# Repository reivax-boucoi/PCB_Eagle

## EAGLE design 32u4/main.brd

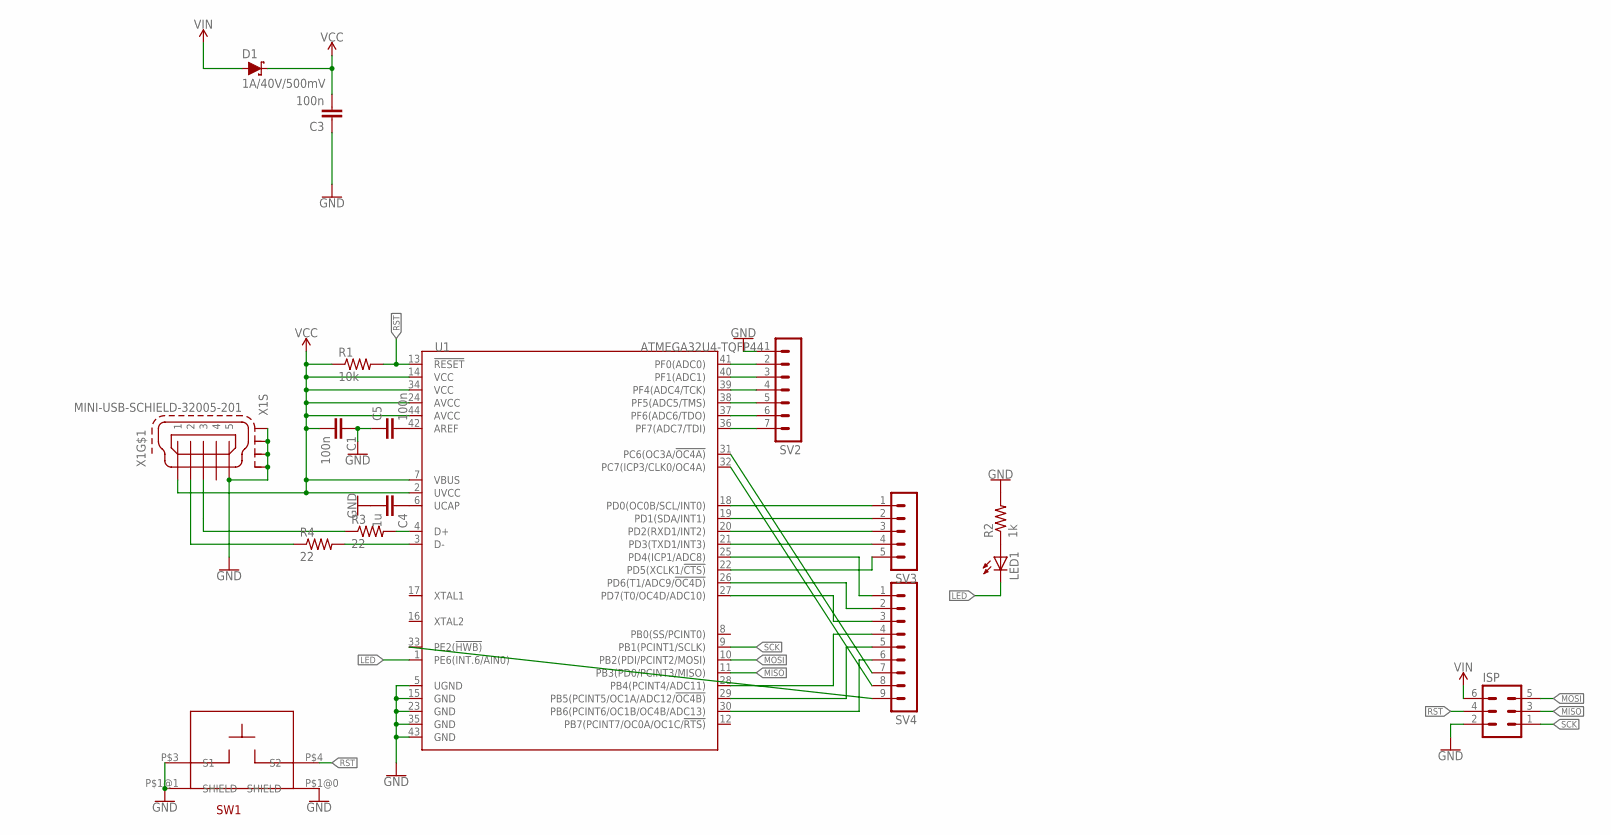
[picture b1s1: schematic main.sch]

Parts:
C1: 100n; C0402
C3, C5: 100n; C0603
C4: 1u; C0603
D1: 1A/40V/500mV; SMA-DIODE
ISP: MA03-2
LED1: LEDCHIP-LED0603; CHIP-LED0603
R1: 10k; R0603
R2: 1k; R0603
R3, R4: 22; R0603
SV2: MA07-1
SV3: MA05-1
SV4: MA09-1
SW1: TL3330
U1: ATMEGA32U4-TQFP44; TQFP44-0.8-9.6X9.6MM
X1: MINI-USB-SCHIELD-32005-201; 32005-201

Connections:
GND: C1.1, C3.1, C4.2, C5.1, ISP.2, R2.2, SV2.1, SW1.P$1@0 (SHIELD), SW1.P$1@1 (SHIELD), SW1.P$3 (S1), U1.5 (UGND), U1.15 (GND), U1.23 (GND), U1.35 (GND), U1.43 (GND), X1.5, X1.M1 (S1), X1.M2 (S2), X1.M3 (S3), X1.M4 (S4)
LED: LED1.C, U1.1 (PE6(INT.6/AIN0))
MISO: ISP.3, U1.11 (PB3(PD0/PCINT3/MISO))
MOSI: ISP.5, U1.10 (PB2(PDI/PCINT2/MOSI))
unnamed: LED1.A, R2.1
unnamed: R4.2, U1.3 (D-)
unnamed: R3.2, U1.4 (D+)
unnamed: SV3.1, U1.18 (PD0(OC0B/SCL/INT0))
unnamed: C4.1, U1.6 (UCAP)
unnamed: C5.2, U1.42 (AREF)
unnamed: SV3.2, U1.19 (PD1(SDA/INT1))
unnamed: SV3.3, U1.20 (PD2(RXD1/INT2))
unnamed: SV3.4, U1.21 (PD3(TXD1/INT3))
unnamed: R4.1, X1.2
unnamed: R3.1, X1.3
unnamed: SV3.5, U1.22 (PD5(XCLK1/!CTS))
unnamed: SV2.2, U1.41 (PF0(ADC0))
unnamed: SV2.3, U1.40 (PF1(ADC1))
unnamed: SV2.4, U1.39 (PF4(ADC4/TCK))
unnamed: SV2.5, U1.38 (PF5(ADC5/TMS))
unnamed: SV2.6, U1.37 (PF6(ADC6/TDO))
unnamed: SV2.7, U1.36 (PF7(ADC7/TDI))
unnamed: SV4.1, U1.25 (PD4(ICP1/ADC8))
unnamed: SV4.2, U1.26 (PD6(T1/ADC9/!OC4D))
unnamed: SV4.3, U1.27 (PD7(T0/OC4D/ADC10))
unnamed: SV4.4, U1.28 (PB4(PCINT4/ADC11))
unnamed: SV4.5, U1.29 (PB5(PCINT5/OC1A/ADC12/!OC4B))
unnamed: SV4.6, U1.30 (PB6(PCINT6/OC1B/OC4B/ADC13))
unnamed: SV4.7, U1.31 (PC6(OC3A/!OC4A))
unnamed: SV4.8, U1.32 (PC7(ICP3/CLK0/OC4A))
unnamed: SV4.9, U1.33 (PE2(!HWB))
RST: ISP.4, R1.2, SW1.P$4 (S2), U1.13 (!RESET)
SCK: ISP.1, U1.9 (PB1(PCINT1/SCLK))
VCC: C1.2, C3.2, D1.C, R1.1, U1.2 (UVCC), U1.7 (VBUS), U1.14 (VCC), U1.24 (AVCC), U1.34 (VCC), U1.44 (AVCC), X1.1
VIN: D1.A, ISP.6

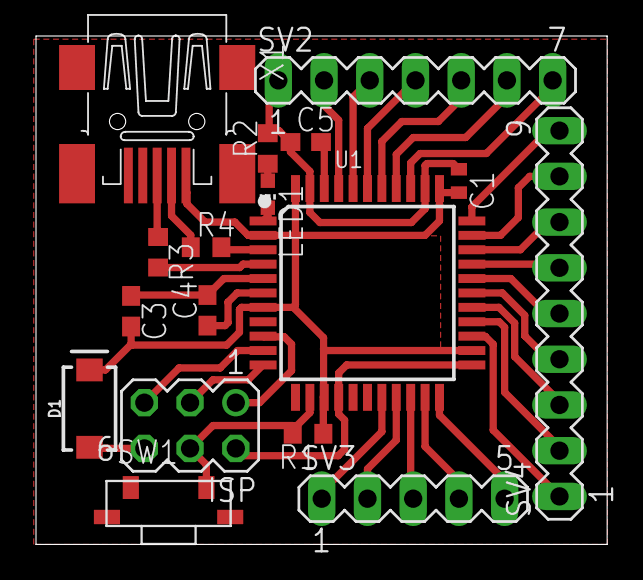
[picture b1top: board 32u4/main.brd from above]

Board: 2 copper layers, 31.7 x 28.2 mm, 17 parts (0 on the bottom side), 35 nets.

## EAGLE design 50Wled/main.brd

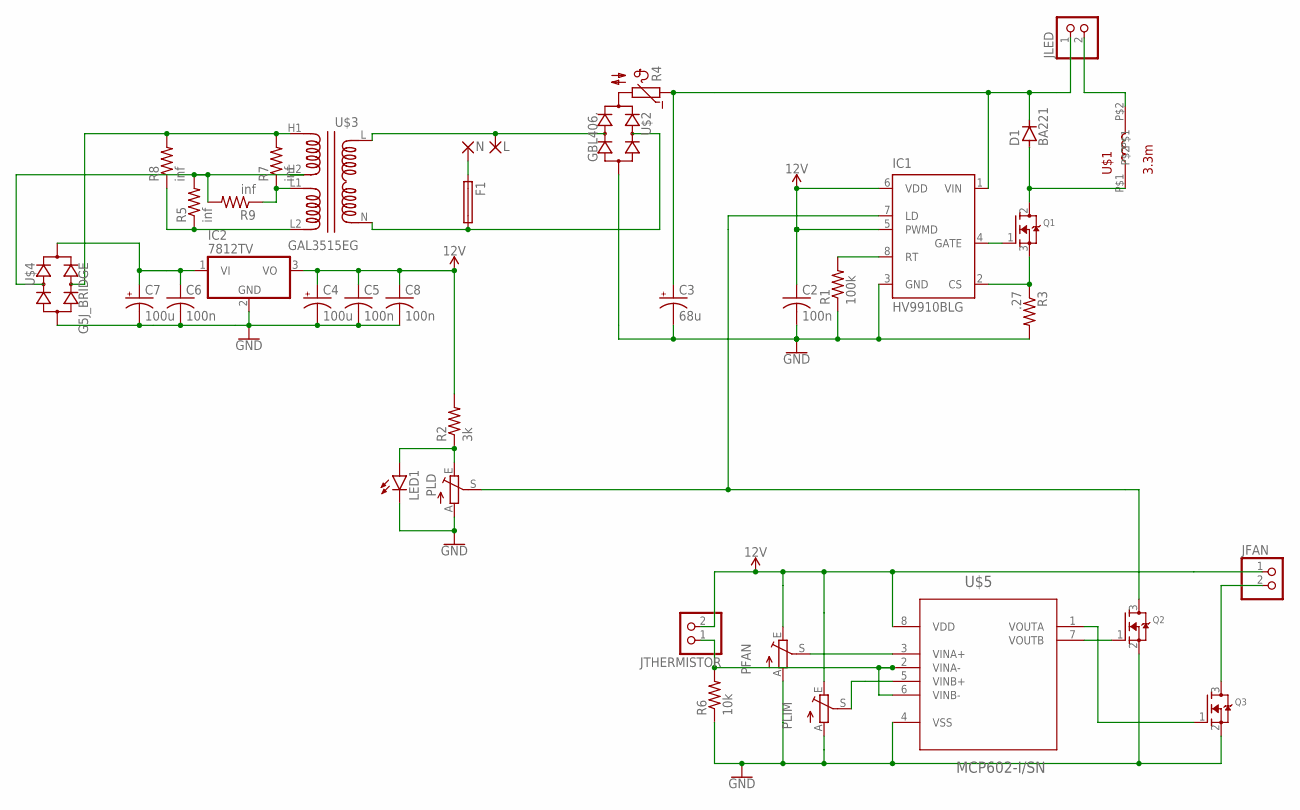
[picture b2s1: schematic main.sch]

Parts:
C2, C5, C6, C8: 100n; C0603
C3: 68u; E7,5-16
C4, C7: 100u; E3,5-8
D1: BA221; DO35-10
F1: SH22,5A
IC1: HV9910BLG; SOIC-08LG
IC2: 7812TV; TO220V
JFAN: PINHD-1X2; 1X02
JLED: PINHD-1X2; 1X02
JTHERMISTOR: PINHD-1X2; 1X02
L: 2,54/1,0
LED1: LED3MM
N: 2,54/1,0
PFAN: TRIM_EU-B64Y; B64Y
PLD: TRIM_EU-B64Y; B64Y
PLIM: TRIM_EU-B64Y; B64Y
Q1: MOSFET-NGDS_TO220V; TO220V
Q2, Q3: MOSFET-NREFLOW; SOT23
R1: 100k; R0603
R2: 3k; 0204/5
R3: .27; 0207/7
R4: B57164
R5, R7, R8, R9: inf; R0805
R6: 10k; R0603
U$1: 3.3m; 3.3MH
U$2: GBL406.; GBL406
U$3: GAL3515EG; GAL3515E
U$4: G5J_BRIDGE
U$5: MCP602-I/SN; SOIC127P600X175-8N

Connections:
12V: C2.1, C4.+, C5.1, C8.1, IC1.5 (PWMD), IC1.6 (VDD), IC2.3 (VO), JFAN.1, JTHERMISTOR.2, PFAN.E, PLIM.E, R2.2, U$5.8 (VDD)
CS: IC1.2 (CS), Q1.3 (S), R3.1
FANMINUS: JFAN.2, Q3.3 (D)
FFAN: Q3.1 (G), U$5.1 (VOUTA)
FLED: Q2.1 (G), U$5.7 (VOUTB)
GATE: IC1.4 (GATE), Q1.1 (G)
GND: C2.2, C3.-, C4.-, C5.2, C6.2, C7.-, C8.2, IC1.3 (GND), IC2.2 (GND), LED1.K (C), PFAN.A, PLD.A, PLIM.A, Q2.2 (S), Q3.2 (S), R1.1, R3.2, R6.1, U$2.-, U$4.-, U$5.4 (VSS)
H1: R7.2, R8.2, U$3.H1, U$4.AC2 (AC)
H2: R5.2, R9.2, U$3.H2, U$4.AC1 (AC)
L: L.1, U$2.AC@2 (AC), U$3.L
LD: IC1.7 (LD), PLD.S, Q2.3 (D)
N: F1.2, U$2.AC@1 (AC), U$3.N
unnamed: D1.A, Q1.2 (D), U$1.P$1
unnamed: R4.2, U$2.+
unnamed: IC1.8 (RT), R1.2
unnamed: F1.1, N.1
unnamed: LED1.A, PLD.E, R2.1
unnamed: JLED.2, U$1.P$2
unnamed: PFAN.S, U$5.3 (VINA+)
unnamed: R7.1, R9.1, U$3.L1
unnamed: JTHERMISTOR.1, R6.2, U$5.2 (VINA-), U$5.6 (VINB-)
unnamed: R5.1, R8.1, U$3.L2
unnamed: C6.1, C7.+, IC2.1 (VI), U$4.+
SETFAULT: PLIM.S, U$5.5 (VINB+)
V+: C3.+, D1.C, IC1.1 (VIN), JLED.1, R4.1

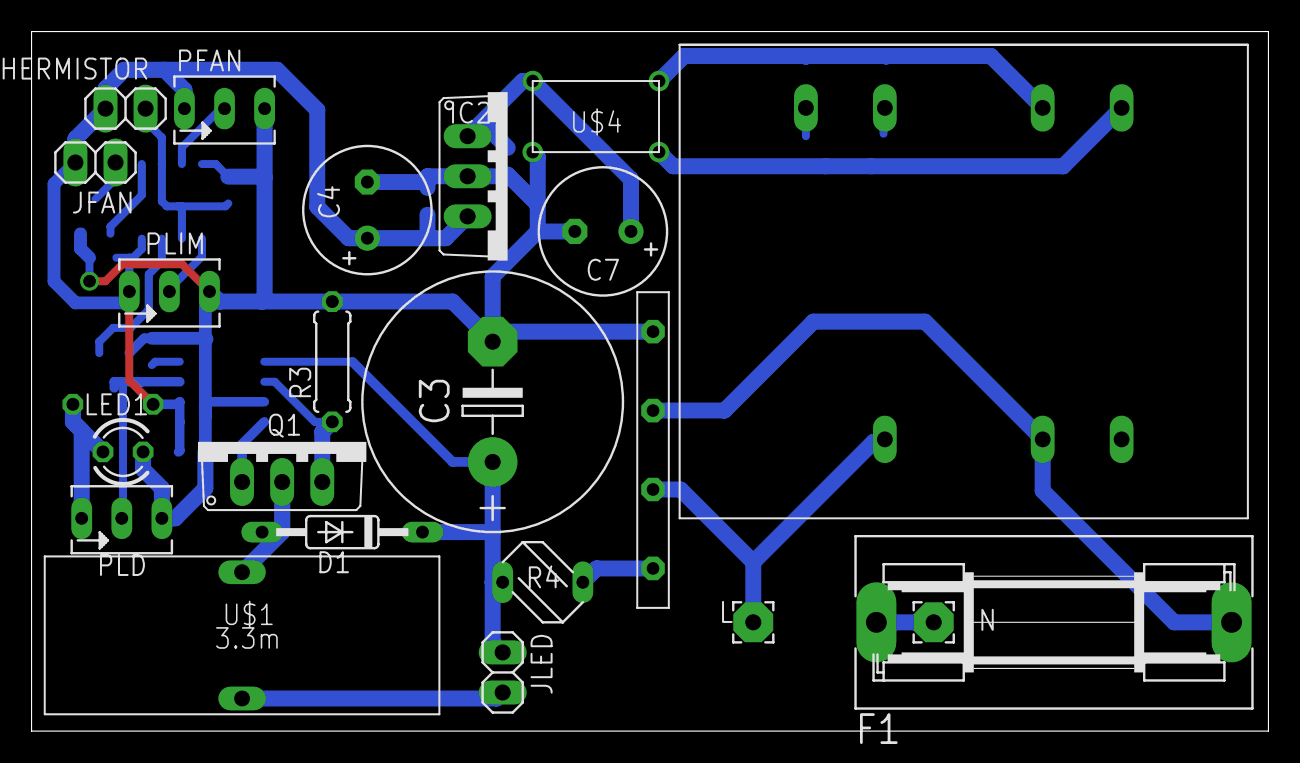
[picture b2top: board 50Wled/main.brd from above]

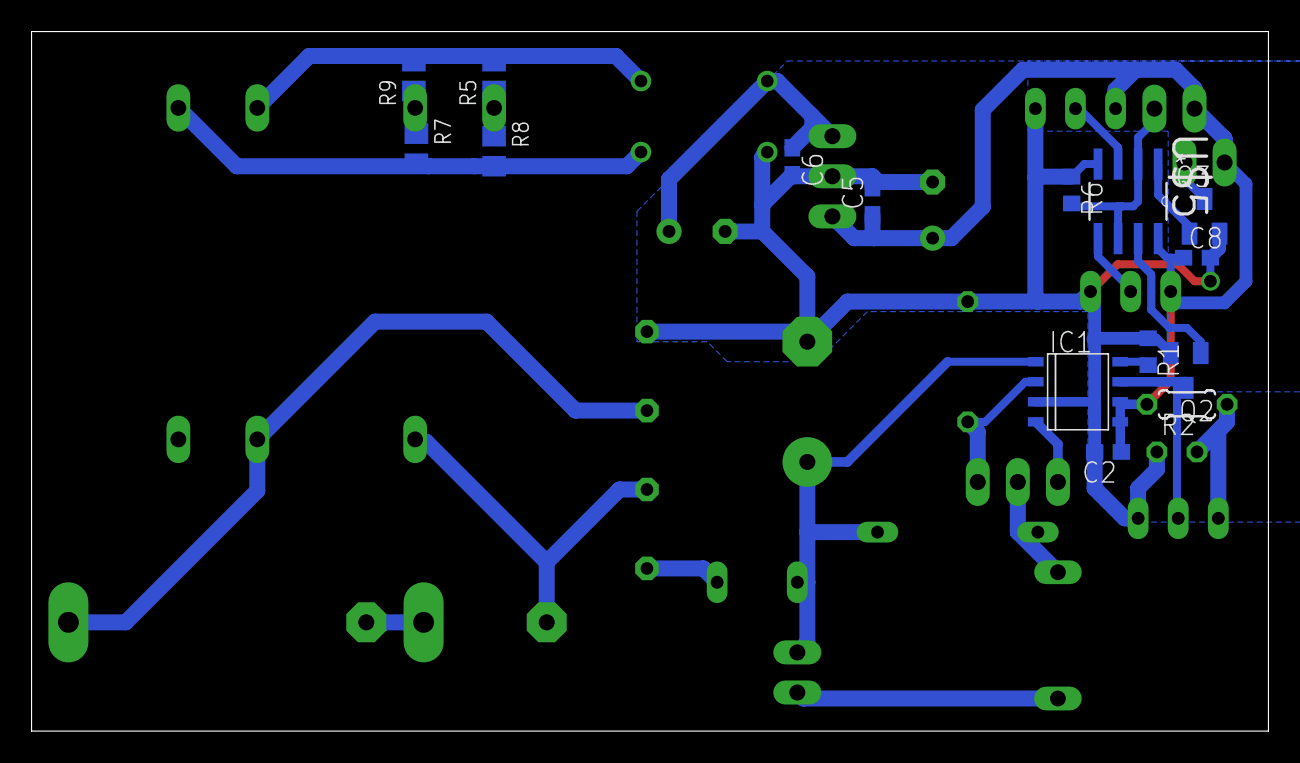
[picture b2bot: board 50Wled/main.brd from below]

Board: 2 copper layers, 78.4 x 44.3 mm, 37 parts (15 on the bottom side), 25 nets.

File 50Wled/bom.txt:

Partlist exported from /media/user/Data/Documents/Eagle_7/50Wled/main.sch at 22/05/2019 23:08

Got Qty Value       Device             Package            Parts                   Description                                                             
0    2               2,54/1,0           2,54/1,0           L, N                    THROUGH-HOLE PAD                                                        
1    1               LED3MM             LED3MM             LED1                    LED                                                                     
1    1               MOSFET-NGDS_TO220V TO220V             Q1                      N-Channel Mosfet                                                        
2    2               MOSFET-NREFLOW     SOT23              Q2, Q3                  N-Channel Mosfet                                                        
3    3               PINHD-1X2          1X02               JFAN, JLED, JTHERMISTOR PIN HEADER                                                              
1    1               SH22,5A            SH22,5A            F1                      FUSE HOLDER grid 22,5mm, isolated cap OGN0031 8201, Schurter (Buerklin) 
1    1   .27         R-US_0207/7        0207/7             R3                      RESISTOR, American symbol                                               
2    2   100u        CPOL-USE3.5-8      E3,5-8             C4, C7                  POLARIZED CAPACITOR, American symbol                                    
1    1   3.3m        3.3MH              3.3MH              U$1                                                                                             
1    1   68u         CPOL-USE7.5-16     E7,5-16            C3                      POLARIZED CAPACITOR, American symbol                                    
1    1   7812TV      7812TV             TO220V             IC2                     Positive VOLTAGE REGULATOR                                              
1    1   BA221       BA221              DO35-10            D1                      DIODE                                                                   
1    1   G5J_BRIDGE  G5J_BRIDGE         G5J_BRIDGE         U$4                                                                                             
1    1   GAL3515EG   GAL3515EG          GAL3515E           U$3                                                                                             
1    1   GBL406.     GBL406.            GBL406             U$2                                                                                             
1    1   HV9910BLG   HV9910BLG          SOIC-08LG          IC1                     Universal High Brightness LED Driver                                    
1    1   MCP602-I/SN MCP602-I/SN        SOIC127P600X175-8N U$5                     CMOS Op Amp                                                             
0    4   inf         R-US_R0805         R0805              R5, R7, R8, R9          RESISTOR, American symbol                                               
    1               B57164             B57164             R4                      SIEMENS NTC                                                             
    3               TRIM_EU-B64Y       B64Y               PFAN, PLD, PLIM         POTENTIOMETER                                                           
    1   100k        R-US_R0603         R0603              R1                      RESISTOR, American symbol                                               
    4   100n        C-USC0603          C0603              C2, C5, C6, C8          CAPACITOR, American symbol                                              
    1   10k         R-US_R0603         R0603              R6                      RESISTOR, American symbol                                               
    1   3k(tocheck) R-US_0204/5        0204/5             R2                      RESISTOR, American symbol

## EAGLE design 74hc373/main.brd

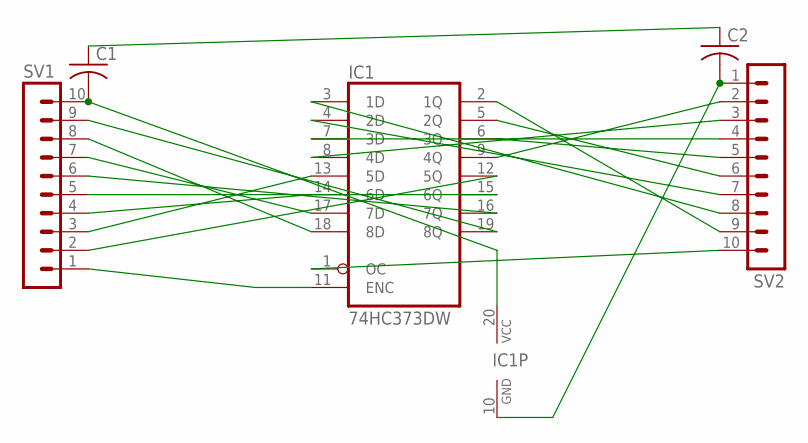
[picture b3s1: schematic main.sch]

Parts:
C1, C2: C-USC0603; C0603
IC1: 74HC373DW; SO20W
SV1, SV2: MA10-1

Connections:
unnamed: IC1.1 (OC), SV2.10
unnamed: IC1.18 (8D), SV1.8
unnamed: IC1.17 (7D), SV1.7
unnamed: IC1.14 (6D), SV1.4
unnamed: IC1.13 (5D), SV1.3
unnamed: IC1.3 (1D), SV2.8
unnamed: IC1.4 (2D), SV2.7
unnamed: IC1.12 (5Q), SV1.2
unnamed: IC1.15 (6Q), SV1.5
unnamed: IC1.2 (1Q), SV2.9
unnamed: IC1.5 (2Q), SV2.6
unnamed: IC1.6 (3Q), SV2.5
unnamed: IC1.9 (4Q), SV2.2
unnamed: IC1.16 (7Q), SV1.6
unnamed: IC1.19 (8Q), SV1.9
unnamed: IC1.7 (3D), SV2.4
unnamed: IC1.8 (4D), SV2.3
unnamed: IC1.11 (ENC), SV1.1
unnamed: C1.2, IC1.20 (VCC), SV1.10
unnamed: C2.2, IC1.10 (GND), SV2.1
unnamed: C1.1, C2.1

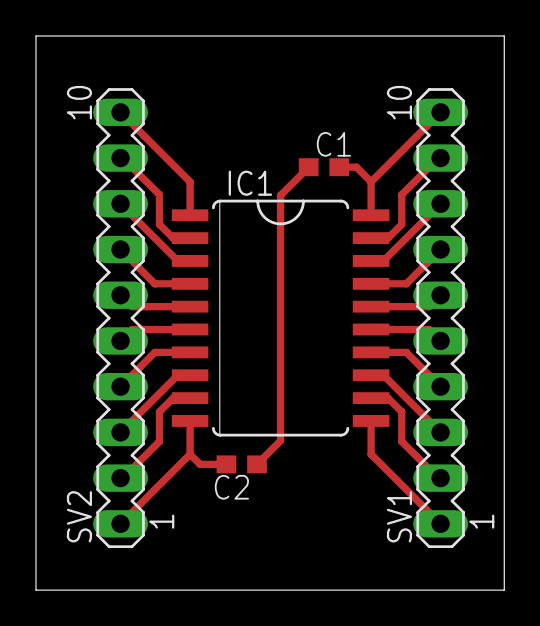
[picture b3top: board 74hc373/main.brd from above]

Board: 2 copper layers, 26.0 x 30.8 mm, 5 parts (0 on the bottom side), 21 nets.

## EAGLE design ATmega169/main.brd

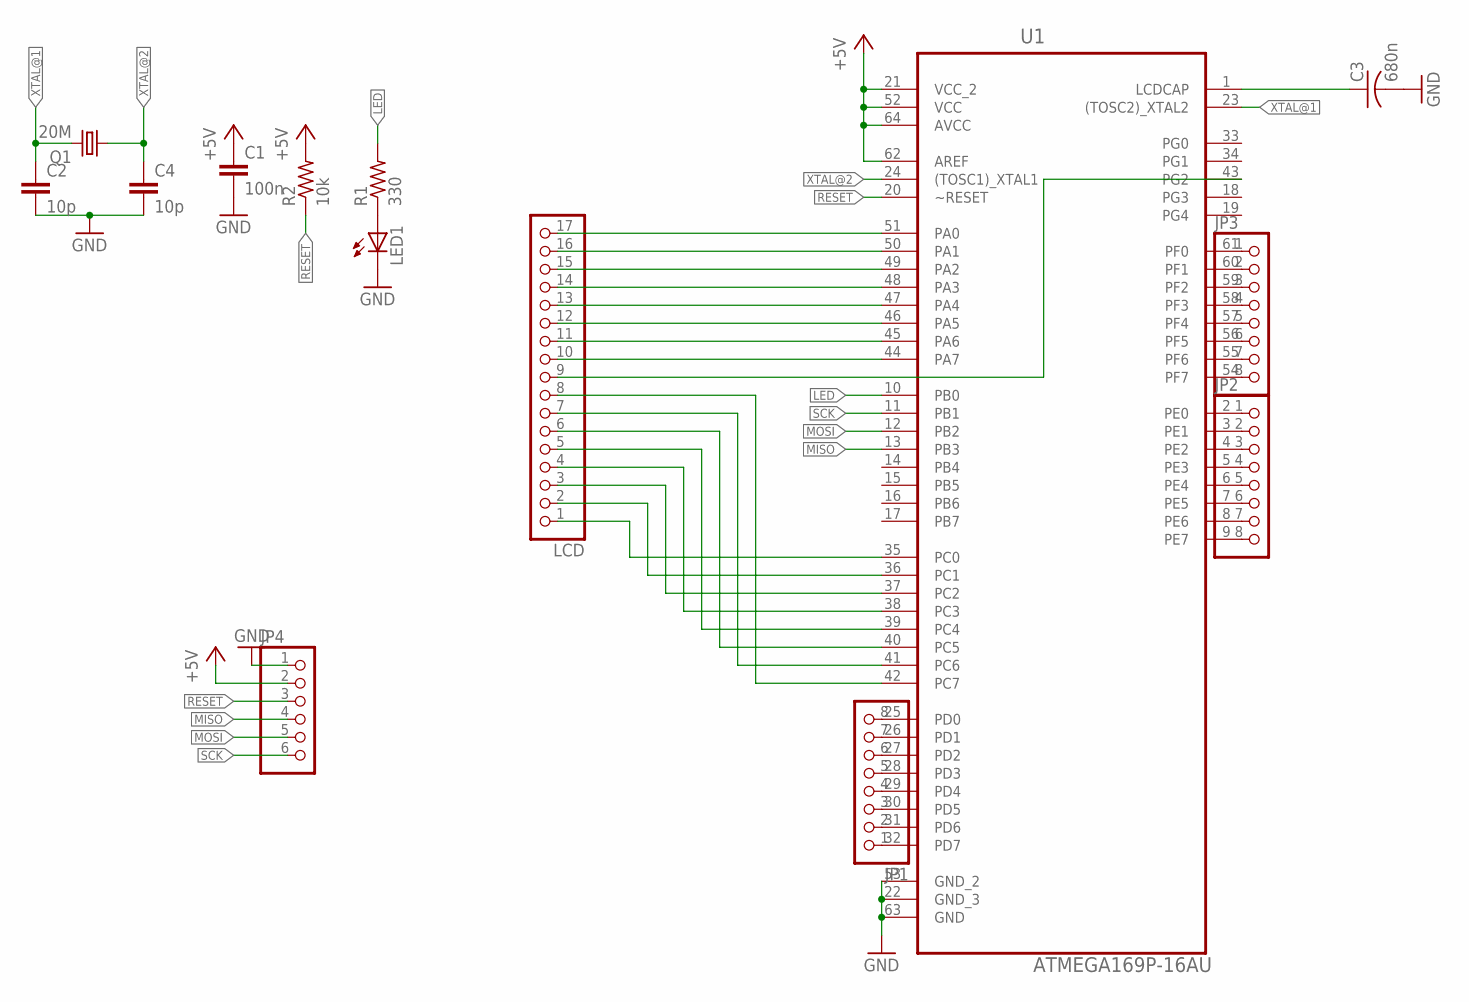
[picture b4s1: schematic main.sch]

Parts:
C1: 100n; C0603
C2, C4: 10p; C0603
C3: 680n; C025-025X050
JP1, JP2, JP3: PINHD-1X8/90; 1X08/90
JP4: PINHD-1X6; 1X06
LCD: PINHD-1X17; 1X17
LED1: LEDCHIPLED_0805; CHIPLED_0805
Q1: 20M; HC49UP
R1: 330; R0603
R2: 10k; R0603
U1: ATMEGA169P-16AU; QFP80P1600X1600X120-64N

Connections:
+5V: C1.1, JP4.2, R2.2, U1.21 (VCC_2), U1.52 (VCC), U1.62 (AREF), U1.64 (AVCC)
GND: C1.2, C2.2, C3.2, C4.2, JP4.1, LED1.C, U1.22 (GND_3), U1.53 (GND_2), U1.63 (GND)
LED: R1.2, U1.10 (PB0)
MISO: JP4.4, U1.13 (PB3)
MOSI: JP4.5, U1.12 (PB2)
unnamed: LED1.A, R1.1
unnamed: LCD.9, U1.43 (PG2)
unnamed: LCD.8, U1.42 (PC7)
unnamed: C3.1, U1.1 (LCDCAP)
unnamed: LCD.7, U1.41 (PC6)
unnamed: LCD.6, U1.40 (PC5)
unnamed: LCD.5, U1.39 (PC4)
unnamed: LCD.10, U1.44 (PA7)
unnamed: LCD.11, U1.45 (PA6)
unnamed: LCD.12, U1.46 (PA5)
unnamed: LCD.13, U1.47 (PA4)
unnamed: LCD.14, U1.48 (PA3)
unnamed: LCD.15, U1.49 (PA2)
unnamed: LCD.16, U1.50 (PA1)
unnamed: LCD.17, U1.51 (PA0)
unnamed: LCD.4, U1.38 (PC3)
unnamed: LCD.3, U1.37 (PC2)
unnamed: LCD.2, U1.36 (PC1)
unnamed: LCD.1, U1.35 (PC0)
unnamed: JP1.1, U1.32 (PD7)
unnamed: JP1.2, U1.31 (PD6)
unnamed: JP1.3, U1.30 (PD5)
unnamed: JP1.4, U1.29 (PD4)
unnamed: JP1.5, U1.28 (PD3)
unnamed: JP1.6, U1.27 (PD2)
unnamed: JP1.7, U1.26 (PD1)
unnamed: JP1.8, U1.25 (PD0)
unnamed: JP2.1, U1.2 (PE0)
unnamed: JP2.2, U1.3 (PE1)
unnamed: JP2.3, U1.4 (PE2)
unnamed: JP2.4, U1.5 (PE3)
unnamed: JP2.5, U1.6 (PE4)
unnamed: JP2.6, U1.7 (PE5)
unnamed: JP2.7, U1.8 (PE6)
unnamed: JP2.8, U1.9 (PE7)
unnamed: JP3.1, U1.61 (PF0)
unnamed: JP3.2, U1.60 (PF1)
unnamed: JP3.3, U1.59 (PF2)
unnamed: JP3.4, U1.58 (PF3)
unnamed: JP3.5, U1.57 (PF4)
unnamed: JP3.6, U1.56 (PF5)
unnamed: JP3.7, U1.55 (PF6)
unnamed: JP3.8, U1.54 (PF7)
RESET: JP4.3, R2.1, U1.20 (~RESET)
SCK: JP4.6, U1.11 (PB1)
XTAL@1: C2.1, Q1.2, U1.23 ((TOSC2)_XTAL2)
XTAL@2: C4.1, Q1.1, U1.24 ((TOSC1)_XTAL1)

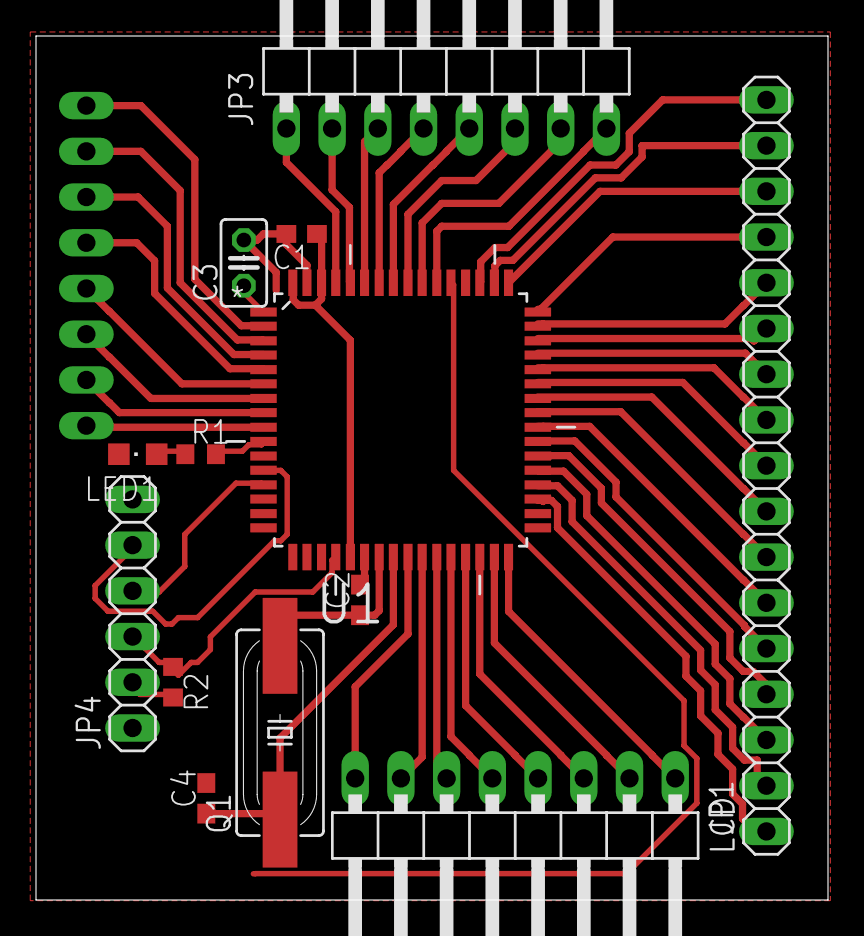
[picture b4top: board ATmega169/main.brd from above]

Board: 2 copper layers, 44.0 x 48.0 mm, 14 parts (1 on the bottom side), 52 nets.

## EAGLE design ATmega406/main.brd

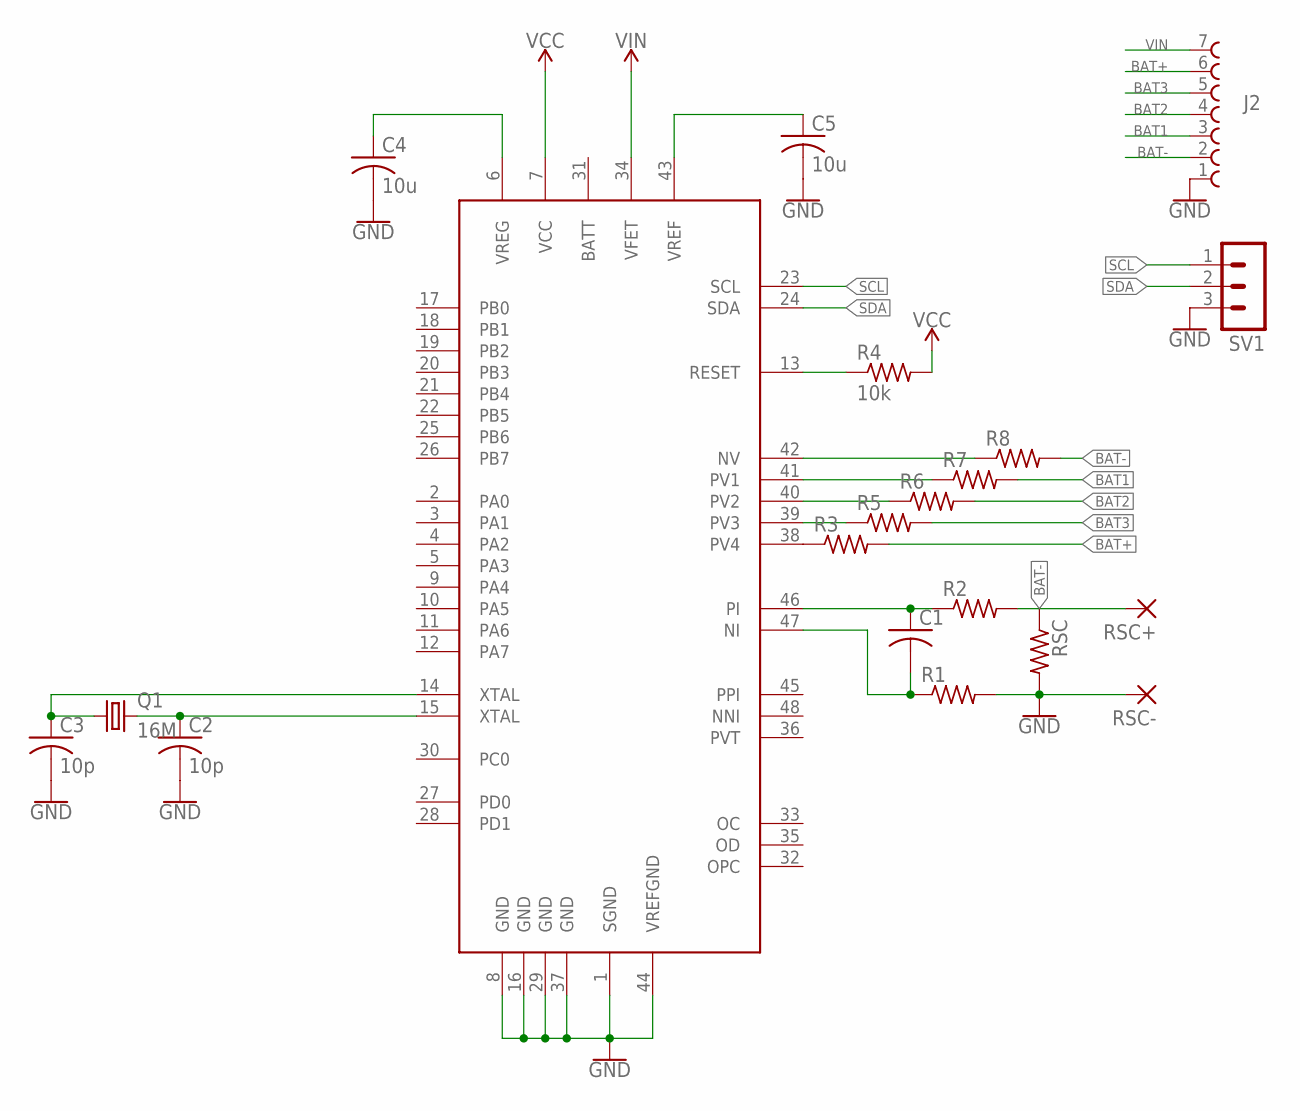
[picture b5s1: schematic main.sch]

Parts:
C1: C-USC0805; C0805
C2, C3: 10p; C0805
C4, C5: 10u; C0805
J2: 691136710007
Q1: 16M; HC49U-V
R1, R2, R3, R5, R6, R7, R8: R-US_R0805; R0805
R4: 10k; R0603
RSC: R-US_R0805; R0805
RSC+: 2,54/1,0
RSC-: 2,54/1,0
SV1: MA03-1
U$1: ATMEGA406; LQFP48

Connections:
BAT1: J2.3, R7.2
BAT2: J2.4, R6.2
BAT3: J2.5, R5.2
BAT+: J2.6, R3.2
BAT-: J2.2, R2.2, R8.2, RSC.1, RSC+.1
GND: C2.2, C3.2, C4.2, C5.2, J2.1, R1.2, RSC.2, RSC-.1, SV1.3, U$1.1 (SGND), U$1.8 (GND), U$1.16 (GND), U$1.29 (GND), U$1.37 (GND), U$1.44 (VREFGND)
unnamed: C4.1, U$1.6 (VREG)
unnamed: C1.1, R2.1, U$1.46 (PI)
unnamed: R3.1, U$1.38 (PV4)
unnamed: R5.1, U$1.39 (PV3)
unnamed: C1.2, R1.1, U$1.47 (NI)
unnamed: C2.1, Q1.2, U$1.15 (XTAL)
unnamed: C3.1, Q1.1, U$1.14 (XTAL)
unnamed: R4.1, U$1.13 (RESET)
unnamed: C5.1, U$1.43 (VREF)
unnamed: R6.1, U$1.40 (PV2)
unnamed: R7.1, U$1.41 (PV1)
unnamed: R8.1, U$1.42 (NV)
SCL: SV1.1, U$1.23 (SCL)
SDA: SV1.2, U$1.24 (SDA)
VCC: R4.2, U$1.7 (VCC)
VIN: J2.7, U$1.34 (VFET)

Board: 2 copper layers, 20 parts (0 on the bottom side), 22 nets, no tracks yet.

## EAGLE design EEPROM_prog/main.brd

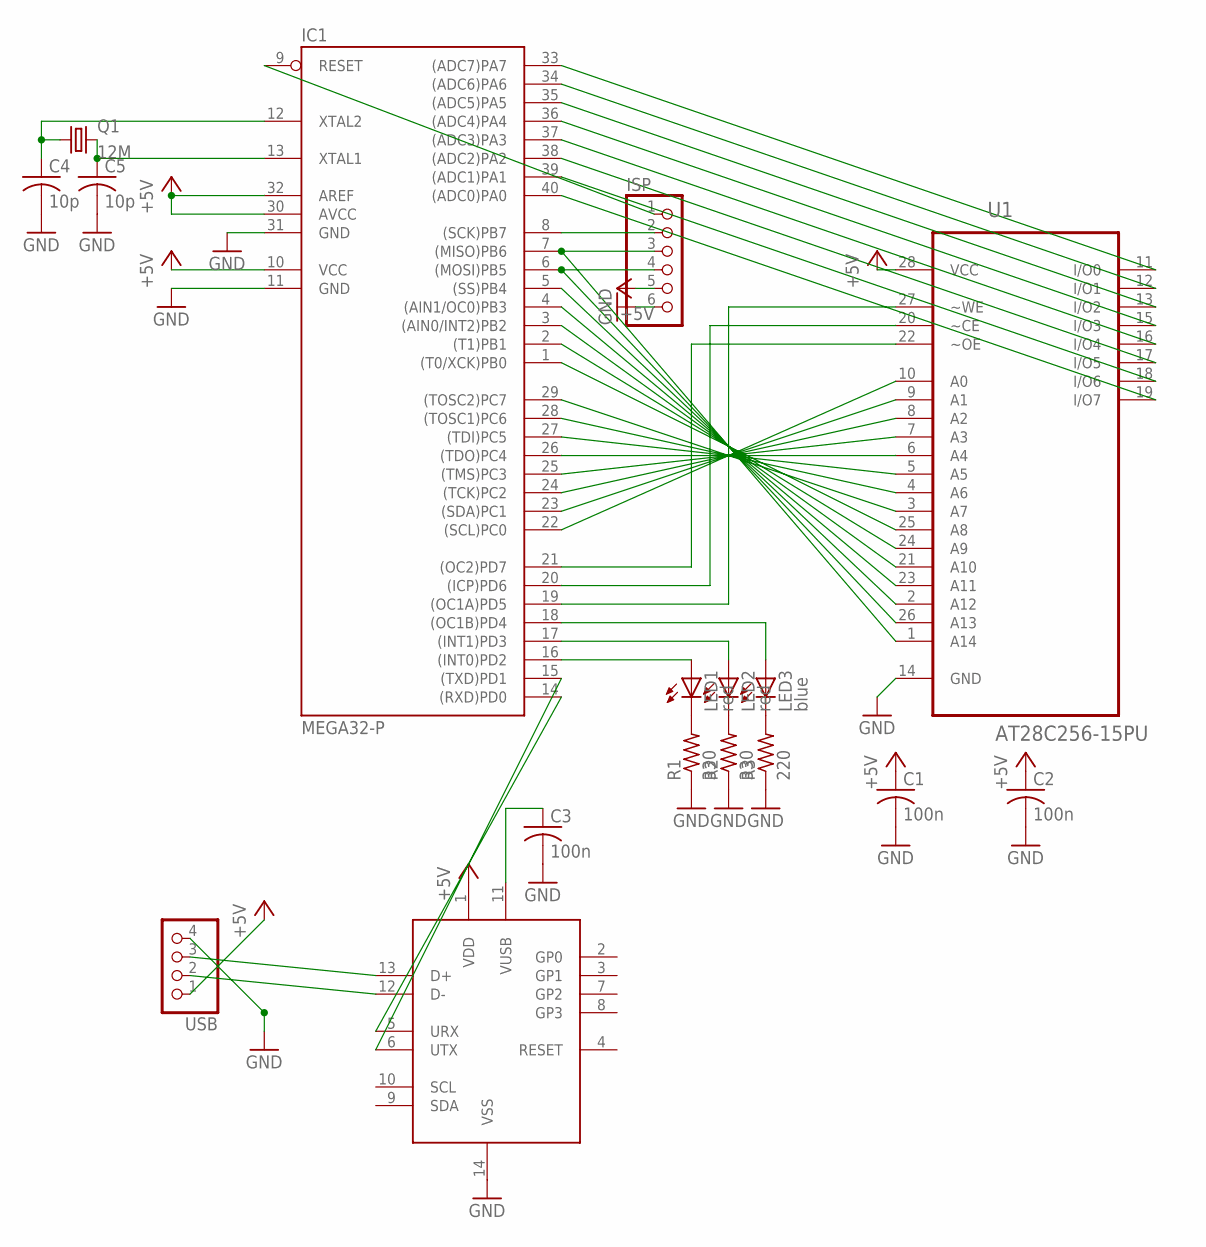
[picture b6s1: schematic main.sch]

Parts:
BR1: MCP2221A; DIP14
C1, C2, C3: 100n; C0603
C4, C5: 10p; C0603
IC1: MEGA32-P; DIL40
ISP: PINHD-1X6; 1X06
LED1, LED2: red; LED5MM
LED3: blue; LED5MM
Q1: 12M; HC49/S
R1, R2: 330; R0805
R3: 220; R0805
U1: AT28C256-15PU; DIP254P1524X482-28
USB: PINHD-1X4; 1X04

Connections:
+5V: BR1.1 (VDD), C1.1, C2.1, IC1.10 (VCC), IC1.30 (AVCC), IC1.32 (AREF), ISP.5, U1.28 (VCC), USB.1
GND: BR1.14 (VSS), C1.2, C2.2, C3.2, C4.2, C5.2, IC1.11 (GND), IC1.31 (GND), ISP.6, R1.1, R2.1, R3.1, U1.14 (GND), USB.4
unnamed: LED1.K (C), R1.2
unnamed: IC1.33 ((ADC7)PA7), U1.11 (I/O0)
unnamed: IC1.34 ((ADC6)PA6), U1.12 (I/O1)
unnamed: IC1.35 ((ADC5)PA5), U1.13 (I/O2)
unnamed: IC1.36 ((ADC4)PA4), U1.15 (I/O3)
unnamed: IC1.37 ((ADC3)PA3), U1.16 (I/O4)
unnamed: IC1.38 ((ADC2)PA2), U1.17 (I/O5)
unnamed: IC1.39 ((ADC1)PA1), U1.18 (I/O6)
unnamed: IC1.40 ((ADC0)PA0), U1.19 (I/O7)
unnamed: LED2.K (C), R2.2
unnamed: IC1.16 ((INT0)PD2), LED1.A
unnamed: IC1.17 ((INT1)PD3), LED2.A
unnamed: IC1.21 ((OC2)PD7), U1.22 (~OE)
unnamed: IC1.20 ((ICP)PD6), U1.20 (~CE)
unnamed: IC1.19 ((OC1A)PD5), U1.27 (~WE)
unnamed: LED3.K (C), R3.2
unnamed: IC1.18 ((OC1B)PD4), LED3.A
unnamed: BR1.11 (VUSB), C3.1
unnamed: IC1.8 ((SCK)PB7), ISP.2
unnamed: IC1.7 ((MISO)PB6), ISP.3, U1.1 (A14)
unnamed: IC1.6 ((MOSI)PB5), ISP.4, U1.26 (A13)
unnamed: IC1.9 (RESET), ISP.1
unnamed: C4.1, IC1.12 (XTAL2), Q1.1
unnamed: C5.1, IC1.13 (XTAL1), Q1.2
unnamed: IC1.22 ((SCL)PC0), U1.10 (A0)
unnamed: IC1.23 ((SDA)PC1), U1.9 (A1)
unnamed: IC1.24 ((TCK)PC2), U1.8 (A2)
unnamed: IC1.25 ((TMS)PC3), U1.7 (A3)
unnamed: IC1.26 ((TDO)PC4), U1.6 (A4)
unnamed: IC1.27 ((TDI)PC5), U1.5 (A5)
unnamed: IC1.28 ((TOSC1)PC6), U1.4 (A6)
unnamed: IC1.29 ((TOSC2)PC7), U1.3 (A7)
unnamed: IC1.1 ((T0/XCK)PB0), U1.25 (A8)
unnamed: IC1.2 ((T1)PB1), U1.24 (A9)
unnamed: IC1.3 ((AIN0/INT2)PB2), U1.21 (A10)
unnamed: IC1.4 ((AIN1/OC0)PB3), U1.23 (A11)
unnamed: IC1.5 ((SS)PB4), U1.2 (A12)
unnamed: BR1.13 (D+), USB.3
unnamed: BR1.12 (D-), USB.2
unnamed: BR1.5 (URX), IC1.14 ((RXD)PD0)
unnamed: BR1.6 (UTX), IC1.15 ((TXD)PD1)

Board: 2 copper layers, 17 parts (8 on the bottom side), 43 nets, no tracks yet.

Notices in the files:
parts and their libraries:
SparkFun-DiscreteSemi: Licensing: Creative Commons ShareAlike 4.0 International - https://creativecommons.org/licenses/by-sa/4.0
Wurth_Elektronik_Electromechanic_Termina: Copyright: Würth Elektronik
